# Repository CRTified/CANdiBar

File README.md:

# CANdiBar

## IMPORTANT

This project is very experimental. While it works *for me* in my Voron V0.2, do not assume that it
works for you. Proceed at your own risk.

## Pictures

## What is this?

This repository aims to contain a small CAN bus and power distribution
board. However, I wanted to avoid making all devices connected by a stub.

Properties:

 - Seven ports for a 2x3P Molex MicroFit 3.0
 - USB2CAN adapter compatible with candlelight
 - Proper CAN setup (No star topology that makes everythin a stub)
 - Pass-through connection configurable by jumper
 - Termination on last slot (might require pass-through on multiple ports)

## Why?

I wanted to try [atopile](https://atopile.io/) and a simple
distribution board seemed like a great fit to test the whole design
process.

I also wanted to have a sane piece of hardware for simplifying the
wiring in my 3D printer, as the
[Voron v0.2r1](https://vorondesign.com/voron0.2) gets pretty crowded
when using more than two MCUs.

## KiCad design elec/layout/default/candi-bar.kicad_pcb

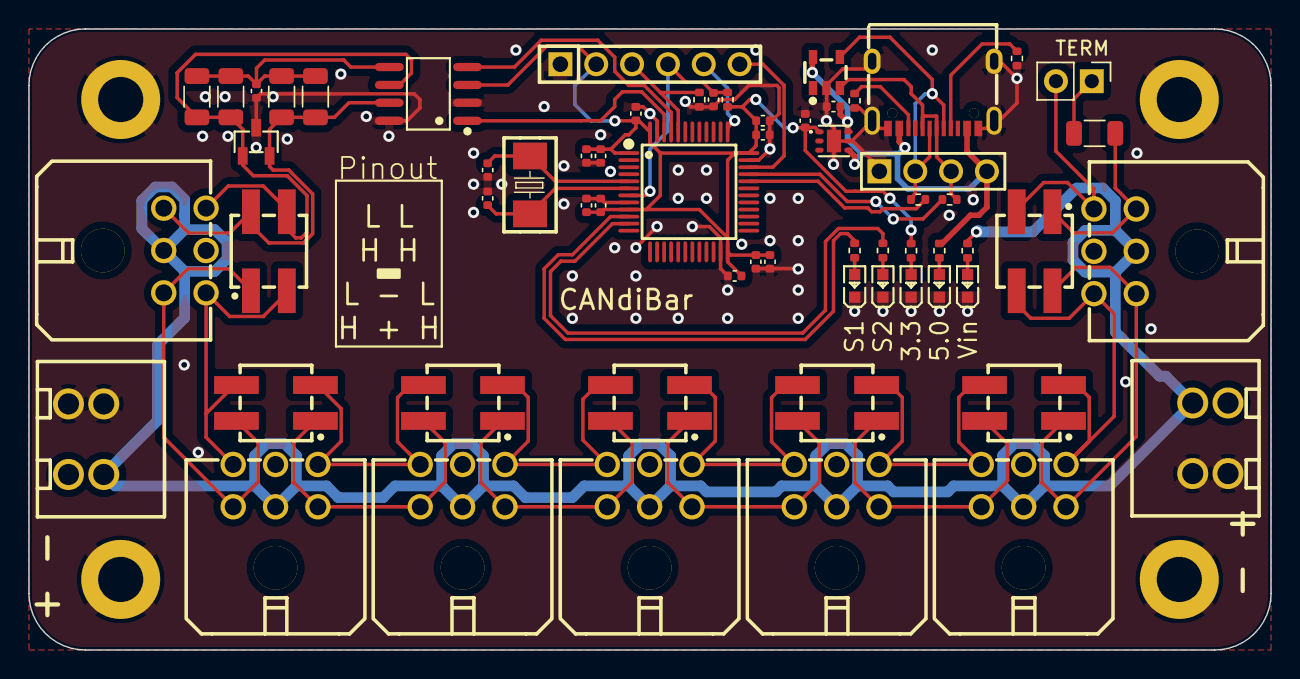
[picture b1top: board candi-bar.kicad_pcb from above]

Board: 4 copper layers, 88.0 x 44.0 mm, 67 parts (0 on the bottom side), 43 nets.

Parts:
C1, C2: 25V 1uF X5R ±10% 0402 Multilayer Ceramic Capacito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; C0402
C3, C4, C5: 10V 4.7uF X5R ±20% 0402 Multilayer Ceramic Capaci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; C0402
C6, C7, C8, C9, C10, C11, C13, C16: 16V 100nF X7R ±10% 0402 Multilayer Ceramic Capaci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; C0402
C12: 50V 4.7nF X7R ±10% 0402 Multilayer Ceramic Capaci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; C0402
C14, C15: 50V 22pF C0G ±5% 0402 Multilayer Ceramic Capacito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; C0402
J1, J2, J3, J4, J5, J6, J7: ?; CONN-TH_43045-0600
JP1, JP2, JP3, JP4, JP5, JP6, JP7: ?; HDR-SMD_4P-P2.54-V-M-R2-C2-LS7.5
JP8: ?; PinHeader_1x02_P2.54mm_Vertical
R1, R2: 62.5mW Thick Film Resistors 50V ±100ppm/℃ ±1% 5.1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; R0402
R3: 62.5mW Thick Film Resistors 50V ±100ppm/℃ ±1% 1kΩ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; R0402
R4, R6, R15: 62.5mW Thick Film Resistors 50V ±100ppm/℃ ±1% 10k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; R0402
R5, R13, R14: 62.5mW Thick Film Resistors 50V ±100ppm/℃ ±1% 510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; R0402
R7, R8, R9, R10, R16: 250mW Thick Film Resistors 200V ±100ppm/℃ ±1% 120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; R1206
R11, R12: 62.5mW Thick Film Resistors 50V ±1% ±100ppm/℃ 22Ω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; R0402
U1, U2, U3, U4: ?; MountingHole_3.2mm_M3_DIN965_Pad
U5, U6: ?; CONN-TH_978-Y-02
U7: ?; USB-C-SMD_TYPE-C-6PIN-2MD-073
U8: ?; SOT-23-5_L2.9-W1.6-P0.95-LS2.8-BR
U9: ?; HDR-TH_4P-P2.54-V-M-1
U10, U11, U12, U19, U20: ?; LED0603-RD
U13: ?; WSON-6_L2.0-W2.0-P0.65-TL-EP
U14: ?; LQFP-48_L7.0-W7.0-P0.50-LS9.0-BL
U15: ?; HDR-TH_6P-P2.54-V-M-A
U16: ?; SOIC-8_L4.9-W3.9-P1.27-LS6.0-BL
U17: ?; SOT-23-3_L2.9-W1.3-P1.90-LS2.4-BR
U18: ?; CRYSTAL-SMD_L5.0-W3.2

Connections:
boot0: R6.1, U14.44, U15.3
candi_u2c.can_trx.ic-vcc: C12.1, R7.2, R8.2, R9.2, R10.2, U16.5
candi_u2c.status_1.LED-a: R13.1, U19.2
candi_u2c.status_2.LED-a: R14.1, U20.2
canh: J1.3, JP1.2, R7.1, R8.1, U16.7, U17.2
canh-1: J1.1, J2.3, JP1.1, JP2.2
canh-2: J2.1, J3.3, JP2.1, JP3.2
canh-3: J3.1, J4.3, JP3.1, JP4.2
canh-4: J4.1, J5.3, JP4.1, JP5.2
canh-5: J5.1, J6.3, JP5.1, JP6.2
canh-6: J6.1, J7.3, JP6.1, JP7.2
canh-7: J7.1, JP7.1, R16.1
canl: J1.6, JP1.4, R9.1, R10.1, U16.6, U17.1
canl-1: J1.4, J2.6, JP1.3, JP2.4
canl-2: J2.4, J3.6, JP2.3, JP3.4
canl-3: J3.4, J4.6, JP3.3, JP4.4
canl-4: J4.4, J5.6, JP4.3, JP5.4
canl-5: J5.4, J6.6, JP5.3, JP6.4
canl-6: J6.4, J7.6, JP6.3, JP7.4
canl-7: J7.4, JP7.3, JP8.2
cc1: R1.1, U7.4
cc2: R2.1, U7.10
dm: R12.2, U7.5, U7.7, U8.4, U9.2
dp: R11.2, U7.6, U7.8, U8.3, U9.3
gnd: C1.2, C2.2, C3.2, C4.2, C5.2, C6.2, C7.2, C8.2, C9.2, C10.2, C11.2, C12.2, C13.2, C14.1, C15.1, C16.2, J1.5, J2.5, J3.5, J4.5, J5.5, J6.5, J7.5, R1.2, R2.2, R6.2, U1.1, U2.1, U3.1, U4.1, U5.1, U6.1, U7.1, U7.12, U7.13, U7.14, U8.2, U9.1, U10.1, U11.1, U12.1, U13.5, U13.7, U14.8, U14.23, U14.35, U14.47, U15.1, U16.2, U16.8, U17.3, U19.1, U20.1
nrst: C16.1, R15.1, U14.7, U15.4
p1: JP8.1, R16.2
pa0: R13.2, U14.10
pa1: R14.2, U14.11
pa11: R12.1, U14.32
pa12: R11.1, U14.33
pb8: U14.45, U16.4
pb9: U14.46, U16.1
pf0_slash_osc_in: C14.2, U14.5, U18.1
pf1_slash_osc_out: C15.2, U14.6, U18.2
pwr_3_3_status.LED-a: R5.1, U12.2
status_main.LED-a: R4.1, U11.2
swclk: U14.37, U15.5
swdio: U14.34, U15.6
usb_j1-vcc: C1.1, R3.2, U7.2, U7.11, U8.5, U9.4, U13.4, U13.6
usb_status.LED-a: R3.1, U10.2
vcc: J1.2, J2.2, J3.2, J4.2, J5.2, J6.2, J7.2, R4.2, U5.2, U6.2
vcc-1: C2.1, C3.1, C4.1, C5.1, C6.1, C7.1, C8.1, C9.1, C10.1, C11.1, C13.1, R5.2, R15.2, U13.1, U14.1, U14.9, U14.24, U14.36, U14.48, U15.2, U16.3

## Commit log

2025-03-09 init: Initial commit
2025-03-09 feat: Initialized ato project
2025-03-09 feat: Initial attempt of CAN Hub
2025-03-09 feat: First revision of the CAN bus
2025-03-09 docs: Create README.md
2025-03-09 chore: Create dependabot.yml
2025-03-09 chore(deps): Bump actions/upload-artifact from 3 to 4
    Bumps [actions/upload-artifact](https://github.com/actions/upload-artifact) from 3 to 4.
    - [Release notes](https://github.com/actions/upload-artifact/releases)
    - [Commits](https://github.com/actions/upload-artifact/compare/v3...v4)
    ---
    updated-dependencies:
    - dependency-name: actions/upload-artifact
2025-03-11 feat(pcb): Minor Touchup
2025-03-19 feat: Add additional u2c circutry
2025-03-31 feat: Add u2c and pcb
2025-03-31 chore(deps): update flake.lock
    Flake lock file updates:
    • Updated input 'nixpkgs':
    'github:NixOS/nixpkgs/36fd87baa9083f34f7f5027900b62ee6d09b1f2f?narHash=sha256-Wh7esNh7G24qYleLvgOSY/7HlDUzWaL/n4qzlBePpiw%3D' (2025-03-07)
    → 'github:NixOS/nixpkgs/52faf482a3889b7619003c0daec593a1912fddc1?narHash=sha256-6hl6L/tRnwubHcA4pfUUtk542wn2Om%2BD4UnDhlDW9BE%3D' (2025-03-30)
    • Updated input 'pre-commit-hooks':
    'github:cachix/git-hooks.nix/b5a62751225b2f62ff3147d0a334055ebadcd5cc?narHash=sha256-srpAbmJapkaqGRE3ytf3bj4XshspVR5964OX5LfjDWc%3D' (2025-03-07)
2025-04-02 feat: Semifinal design
2025-04-02 feat: Reworked with SMD Jumpering
2025-04-02 fix: Make silkscreen less ambigous
2025-04-02 docs: Add picture of PCB designer
2025-04-04 feat: Remove silkscreens
2025-04-05 chore(deps): update flake.lock
    Flake lock file updates:
    • Updated input 'nixpkgs':
    'github:NixOS/nixpkgs/52faf482a3889b7619003c0daec593a1912fddc1?narHash=sha256-6hl6L/tRnwubHcA4pfUUtk542wn2Om%2BD4UnDhlDW9BE%3D' (2025-03-30)
    → 'github:NixOS/nixpkgs/2c8d3f48d33929642c1c12cd243df4cc7d2ce434?narHash=sha256-F7n4%2BKOIfWrwoQjXrL2wD9RhFYLs2/GGe/MQY1sSdlE%3D' (2025-04-02)
    • Updated input 'nixpkgs-ato':
    'github:CRTified/nixpkgs/f6a709dc03258fcdee09f4a7a86cacf407627916?narHash=sha256-3gPHHv/2VDrhV3NnxyIPG2jfqpOaF%2BgaEAo3e01hCms%3D' (2025-04-05)
2025-04-05 chore(deps): update flake.lock
    Flake lock file updates:
    • Updated input 'nixpkgs-ato':
    'github:CRTified/nixpkgs/134d39b71414f549e494006e164f352bfc35629f?narHash=sha256-OE%2B%2Bet1lwwfq1BsR9LVB/ENqNpY4YeCcDf6FeL%2BZWfw%3D' (2025-04-05)
    → 'github:CRTified/nixpkgs/9ba0ef597ee012bd23c33773216bd1527d1533aa?narHash=sha256-%2BrU%2BXsC9RbvRIRW62h25Sm3JDKZcjetOLmNJ%2B65o8a4%3D' (2025-04-05)
2025-04-05 chore: Switch to ato v3
2025-04-05 fix: Re-add template for GITHASH
2025-04-06 feat: Allow larger tolerance of status led current
2025-04-06 chore: Pin CI to specific version of atopile
2025-04-06 feat: Switch to other screw terminal for power
2025-04-15 fix: Switch to bigger termination resistors to be able to handle a fault
2025-04-15 docs: Update pictures
2025-04-15 fix: Change silkscreen on left power input
2025-04-15 feat: Switch termination resistor to 1206 to use basic part
2025-08-18 chore(deps): Bump actions/checkout from 4 to 5
    Bumps [actions/checkout](https://github.com/actions/checkout) from 4 to 5.
    - [Release notes](https://github.com/actions/checkout/releases)
    - [Changelog](https://github.com/actions/checkout/blob/main/CHANGELOG.md)
    - [Commits](https://github.com/actions/checkout/compare/v4...v5)
    ---
    updated-dependencies:
2025-08-21 chore(deps): Bump actions/checkout from 4 to 5 (#4)
    Bumps [actions/checkout](https://github.com/actions/checkout) from 4 to 5.
    - [Release notes](https://github.com/actions/checkout/releases)
    - [Changelog](https://github.com/actions/checkout/blob/main/CHANGELOG.md)
    - [Commits](https://github.com/actions/checkout/compare/v4...v5)
    ---
    updated-dependencies:
2025-10-27 chore(deps): Bump actions/upload-artifact from 4 to 5
    Bumps [actions/upload-artifact](https://github.com/actions/upload-artifact) from 4 to 5.
    - [Release notes](https://github.com/actions/upload-artifact/releases)
    - [Commits](https://github.com/actions/upload-artifact/compare/v4...v5)
    ---
    updated-dependencies:
    - dependency-name: actions/upload-artifact
2025-11-24 chore(deps): Bump actions/checkout from 5 to 6
    Bumps [actions/checkout](https://github.com/actions/checkout) from 5 to 6.
    - [Release notes](https://github.com/actions/checkout/releases)
    - [Changelog](https://github.com/actions/checkout/blob/main/CHANGELOG.md)
    - [Commits](https://github.com/actions/checkout/compare/v5...v6)
    ---
    updated-dependencies:
2025-12-15 chore(deps): Bump actions/upload-artifact from 4 to 6
    Bumps [actions/upload-artifact](https://github.com/actions/upload-artifact) from 4 to 6.
    - [Release notes](https://github.com/actions/upload-artifact/releases)
    - [Commits](https://github.com/actions/upload-artifact/compare/v4...v6)
    ---
    updated-dependencies:
    - dependency-name: actions/upload-artifact

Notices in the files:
elec/layout/default/candi-bar.kicad_pcb:
MIT License
